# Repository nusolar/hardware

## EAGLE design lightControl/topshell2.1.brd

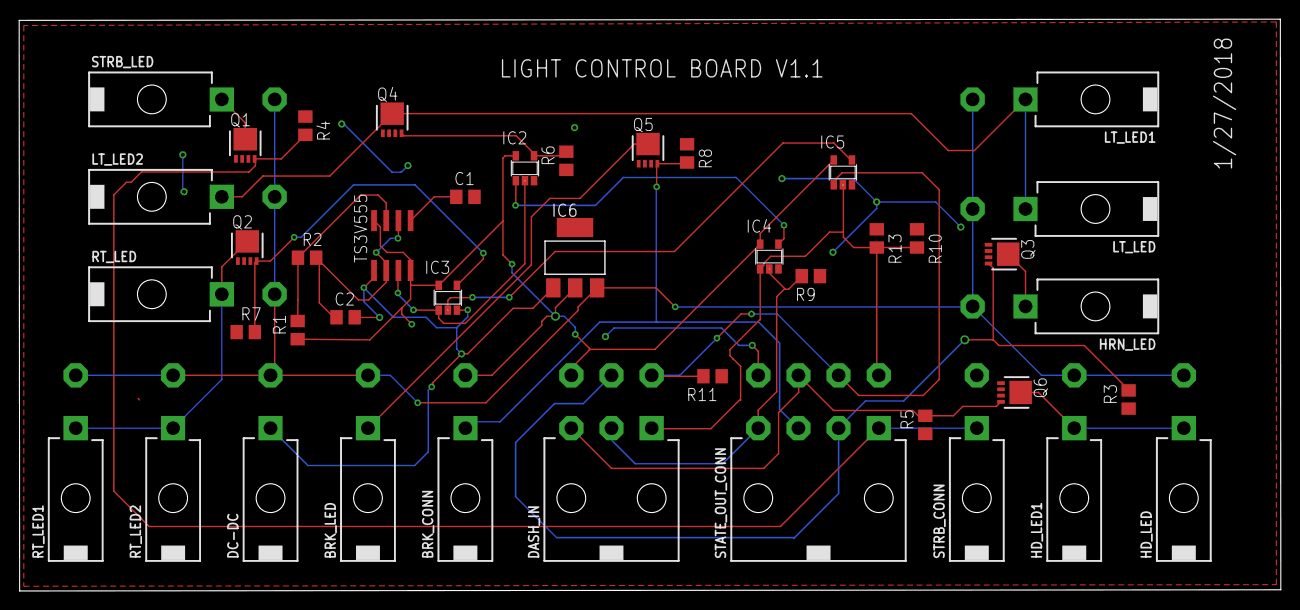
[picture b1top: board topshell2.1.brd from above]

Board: 2 copper layers, 131.6 x 59.6 mm, 42 parts (0 on the bottom side), 24 nets.

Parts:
BRK_CONN: 39-30-02?; 39-30-?02?
BRK_LED: 39-30-02?; 39-30-?02?
C1: 10nF; C0805
C2: 2.2uF; C0805
DASH_IN: 39-30-06?; 39-30-?06?
DC-DC: 39-30-02?; 39-30-?02?
HD_LED, HD_LED1: 39-30-02?; 39-30-?02?
HRN_LED: 39-30-02?; 39-30-?02?
IC2, IC3: 74AHC1G08DBV; SOT23-5
IC4, IC5: 74AHC1G32DBV; SOT23-5
IC6: REG1117; SOT223
LT_LED, LT_LED1, LT_LED2: 39-30-02?; 39-30-?02?
Q1, Q2, Q3, Q4, Q5, Q6: PSMN013-30MLC; LFPAK33
R1: 100K; R0805
R2: 220K; R0805
R3, R4, R5, R6, R7, R8, R9, R10, R11, R13: 1K; R0805
RT_LED, RT_LED1, RT_LED2: 39-30-02?; 39-30-?02?
STATE_OUT_CONN: 39-30-08?; 39-30-?08?
STRB_CONN: 39-30-02?; 39-30-?02?
STRB_LED: 39-30-02?; 39-30-?02?
TS3V555: LM555D; SO08

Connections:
GND: C1.2, C2.2, DC-DC.1, IC2.3, IC3.3, IC4.3, IC5.3, IC6.1, Q1.1, Q1.2, Q1.3, Q2.1, Q2.2, Q2.3, Q3.1, Q3.2, Q3.3, Q4.1, Q4.2, Q4.3, Q5.1, Q5.2, Q5.3, Q6.1, Q6.2, Q6.3, R3.1, R4.1, R5.1, R6.1, R7.1, R8.1, R9.1, R10.1, R11.1, R13.1, STATE_OUT_CONN.8, STRB_CONN.2, TS3V555.1
unnamed: R1.2, R2.1, TS3V555.7
unnamed: Q1.MB, STRB_LED.1
unnamed: C2.1, R2.2, TS3V555.2, TS3V555.6
unnamed: IC2.2, IC3.1, TS3V555.3
unnamed: HRN_LED.1, Q3.MB
unnamed: Q1.4, R4.2, STATE_OUT_CONN.1, STRB_CONN.1
unnamed: DASH_IN.2, IC4.2, R9.2, STATE_OUT_CONN.4
unnamed: DASH_IN.1, IC4.1, IC5.2, R10.2, R13.2, STATE_OUT_CONN.5
unnamed: IC2.1, IC4.4
unnamed: IC3.2, IC5.4
unnamed: DASH_IN.4, IC5.1, R11.2, STATE_OUT_CONN.6
unnamed: IC2.4, Q4.4, R6.2
unnamed: IC3.4, Q2.4, R7.2
unnamed: LT_LED.1, LT_LED1.1, LT_LED2.1, Q4.MB
unnamed: Q2.MB, RT_LED.1, RT_LED1.1, RT_LED2.1
unnamed: BRK_LED.1, Q5.MB
unnamed: HD_LED.1, HD_LED1.1, Q6.MB
unnamed: DASH_IN.3, Q6.4, R5.2, STATE_OUT_CONN.7
unnamed: DASH_IN.5, Q3.4, R3.2, STATE_OUT_CONN.2
unnamed: BRK_CONN.1, Q5.4, R8.2, STATE_OUT_CONN.3
unnamed: BRK_LED.2, DC-DC.2, HD_LED.2, HD_LED1.2, HRN_LED.2, IC6.3, LT_LED.2, LT_LED1.2, LT_LED2.2, RT_LED.2, RT_LED1.2, RT_LED2.2, STRB_LED.2
TS3V555: C1.1, TS3V555.5
VCC: BRK_CONN.2, DASH_IN.6, IC2.5, IC3.5, IC4.5, IC5.5, IC6.2, R1.1, TS3V555.4, TS3V555.8

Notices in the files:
parts and their libraries:
con-molex-mini-fit: Copyright (C) 2011, Bob Starr
transistor-power: PSMN013-30MLC © NXP B.V. 2012. All rights reserved.
